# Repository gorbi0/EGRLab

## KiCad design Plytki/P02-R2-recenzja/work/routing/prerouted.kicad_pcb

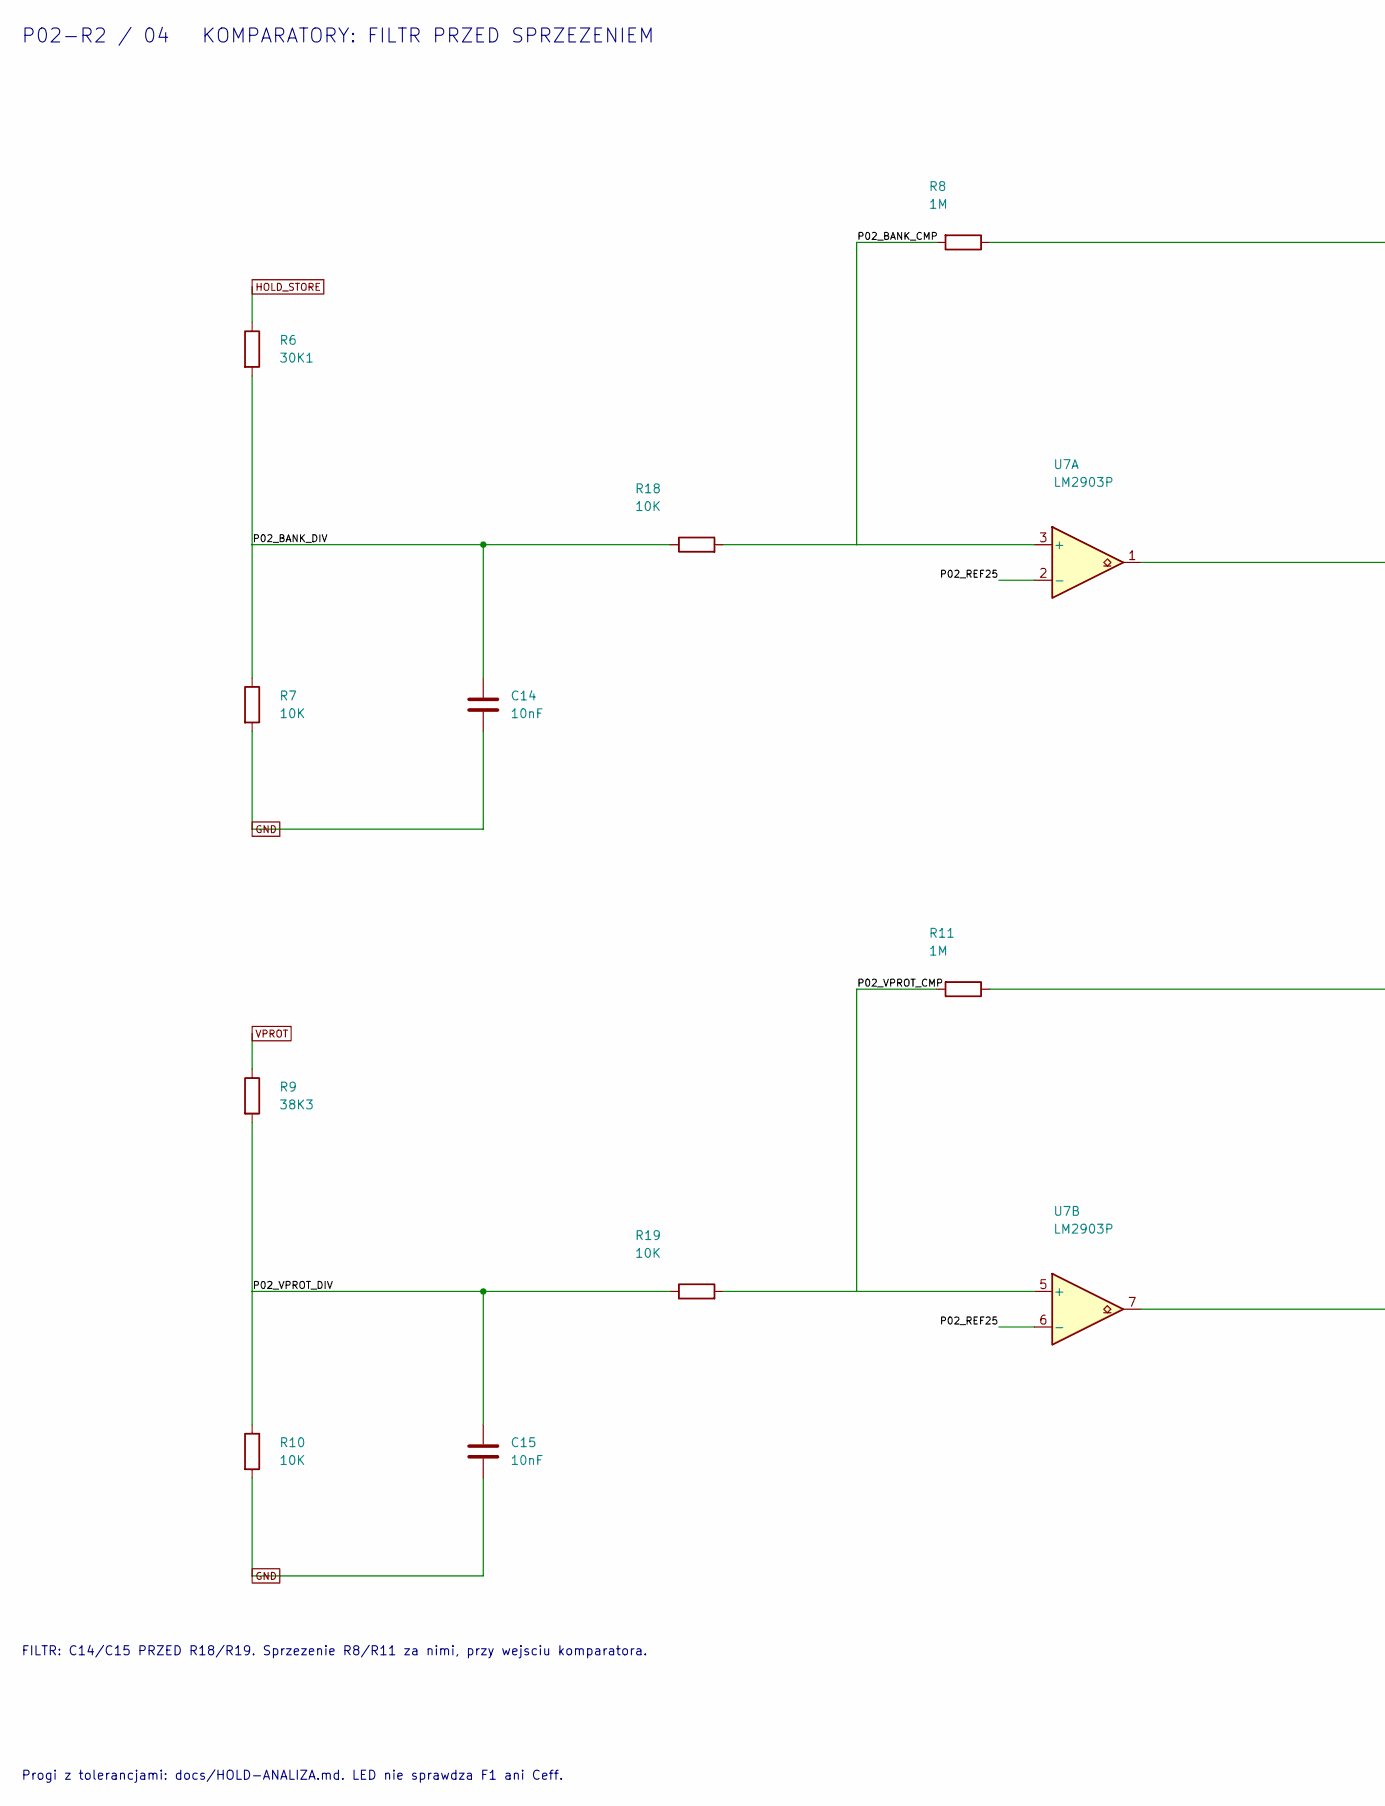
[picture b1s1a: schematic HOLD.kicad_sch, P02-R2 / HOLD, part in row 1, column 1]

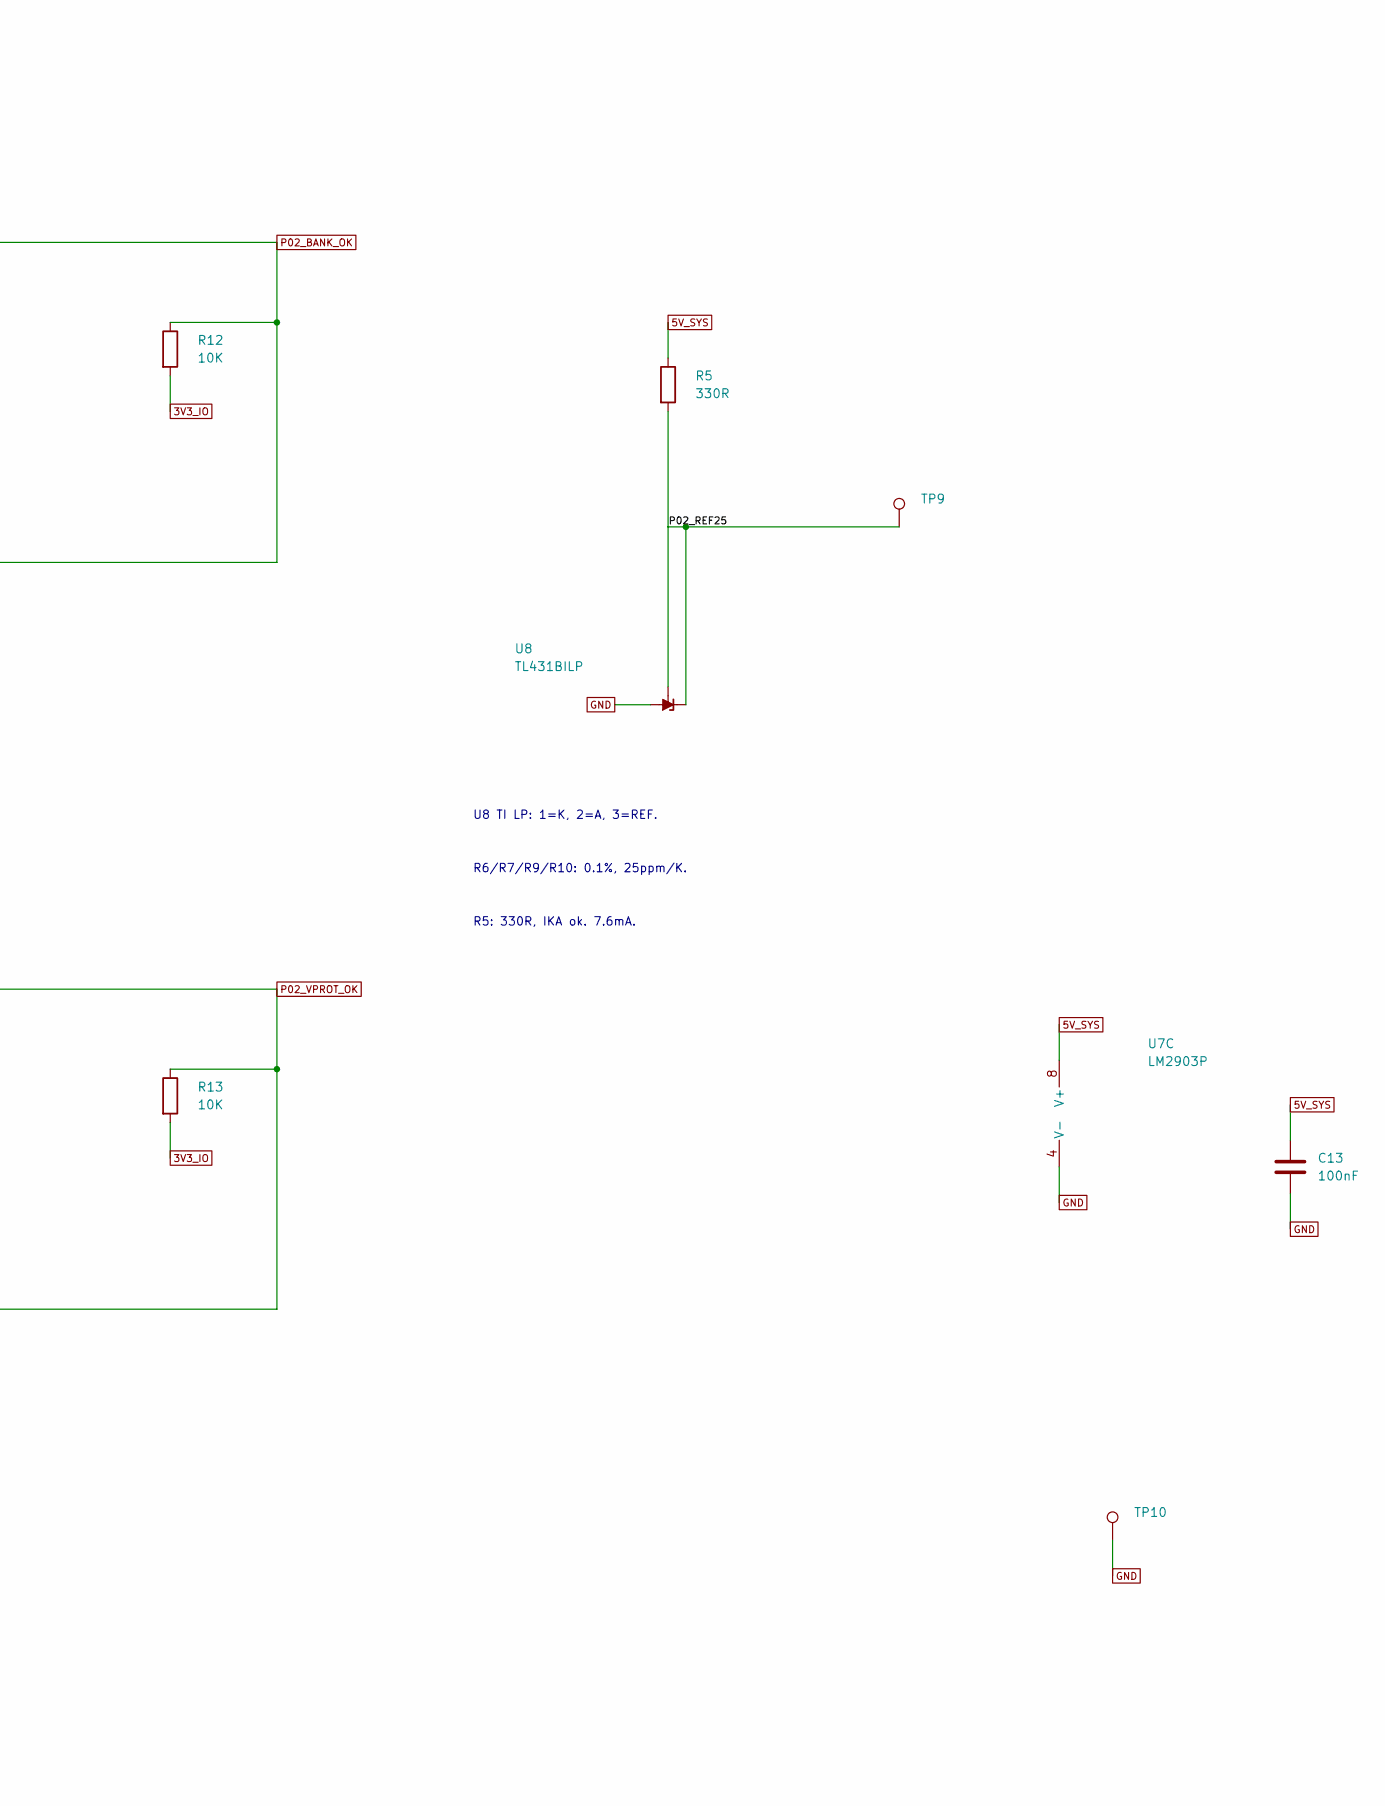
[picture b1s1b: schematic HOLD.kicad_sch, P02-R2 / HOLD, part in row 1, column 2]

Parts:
C13: 100nF; C_Vishay_K15_H5_P5; MPN K104K15X7RF53H5
C14, C15: 10nF; C_Vishay_K15_H5_P5; MPN K103K15X7RF53H5
R5: 330R; R_Axial_DIN0207_L6.3mm_D2.5mm_P10.16mm_Horizontal; MPN MF0207FTE-330R
R6: 30K1; R_Axial_DIN0207_L6.3mm_D2.5mm_P10.16mm_Horizontal; MPN MBB0207VD3012BC100
R7, R10: 10K; R_Axial_DIN0207_L6.3mm_D2.5mm_P10.16mm_Horizontal; MPN MBB0207VD1002BC100
R8, R11: 1M; R_Axial_DIN0207_L6.3mm_D2.5mm_P10.16mm_Horizontal; MPN MF0207FTE-1M
R9: 38K3; R_Axial_DIN0207_L6.3mm_D2.5mm_P10.16mm_Horizontal; MPN MBB0207VD3832BC100
R12, R13, R18, R19: 10K; R_Axial_DIN0207_L6.3mm_D2.5mm_P10.16mm_Horizontal; MPN MF0207FTE-10K
TP9, TP10: TestPad_1; MPN PCB test pad
U7: LM2903P; DIP-8_W7.62mm; MPN LM2903P
U8: TL431BILP; TO-92_Inline_Wide; MPN TL431BILP

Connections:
3V3_IO: R12.2, R13.2; also elsewhere on the board
5V_SYS: C13.1, R5.1, U7.8 (V+); also elsewhere on the board
/HOLD/P02_BANK_CMP: R8.2, R18.2, U7.3 (+)
/HOLD/P02_BANK_DIV: C14.1, R6.2, R7.1, R18.1
/HOLD/P02_REF25: R5.2, TP9.1, U7.2 (-), U7.6 (-), U8.1 (K), U8.3 (REF)
/HOLD/P02_VPROT_CMP: R11.2, R19.2, U7.5 (+)
/HOLD/P02_VPROT_DIV: C15.1, R9.2, R10.1, R19.1
GND: C13.2, C14.2, C15.2, R7.2, R10.2, TP10.1, U7.4 (V-), U8.2 (A); also elsewhere on the board
HOLD_STORE: R6.1; also elsewhere on the board
P02_BANK_OK: R8.1, R12.1, U7.1; also elsewhere on the board
P02_VPROT_OK: R11.1, R13.1, U7.7; also elsewhere on the board
VPROT: R9.1; also elsewhere on the board

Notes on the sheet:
P02-R2 / 04 KOMPARATORY: FILTR PRZED SPRZEZENIEM
FILTR: C14/C15 PRZED R18/R19. Sprzezenie R8/R11 za nimi, przy wejsciu komparatora.
Progi z tolerancjami: docs/HOLD-ANALIZA.md. LED nie sprawdza F1 ani Ceff.
U8 TI LP: 1=K, 2=A, 3=REF.
R6/R7/R9/R10: 0.1%, 25ppm/K.
R5: 330R, IKA ok. 7.6mA.

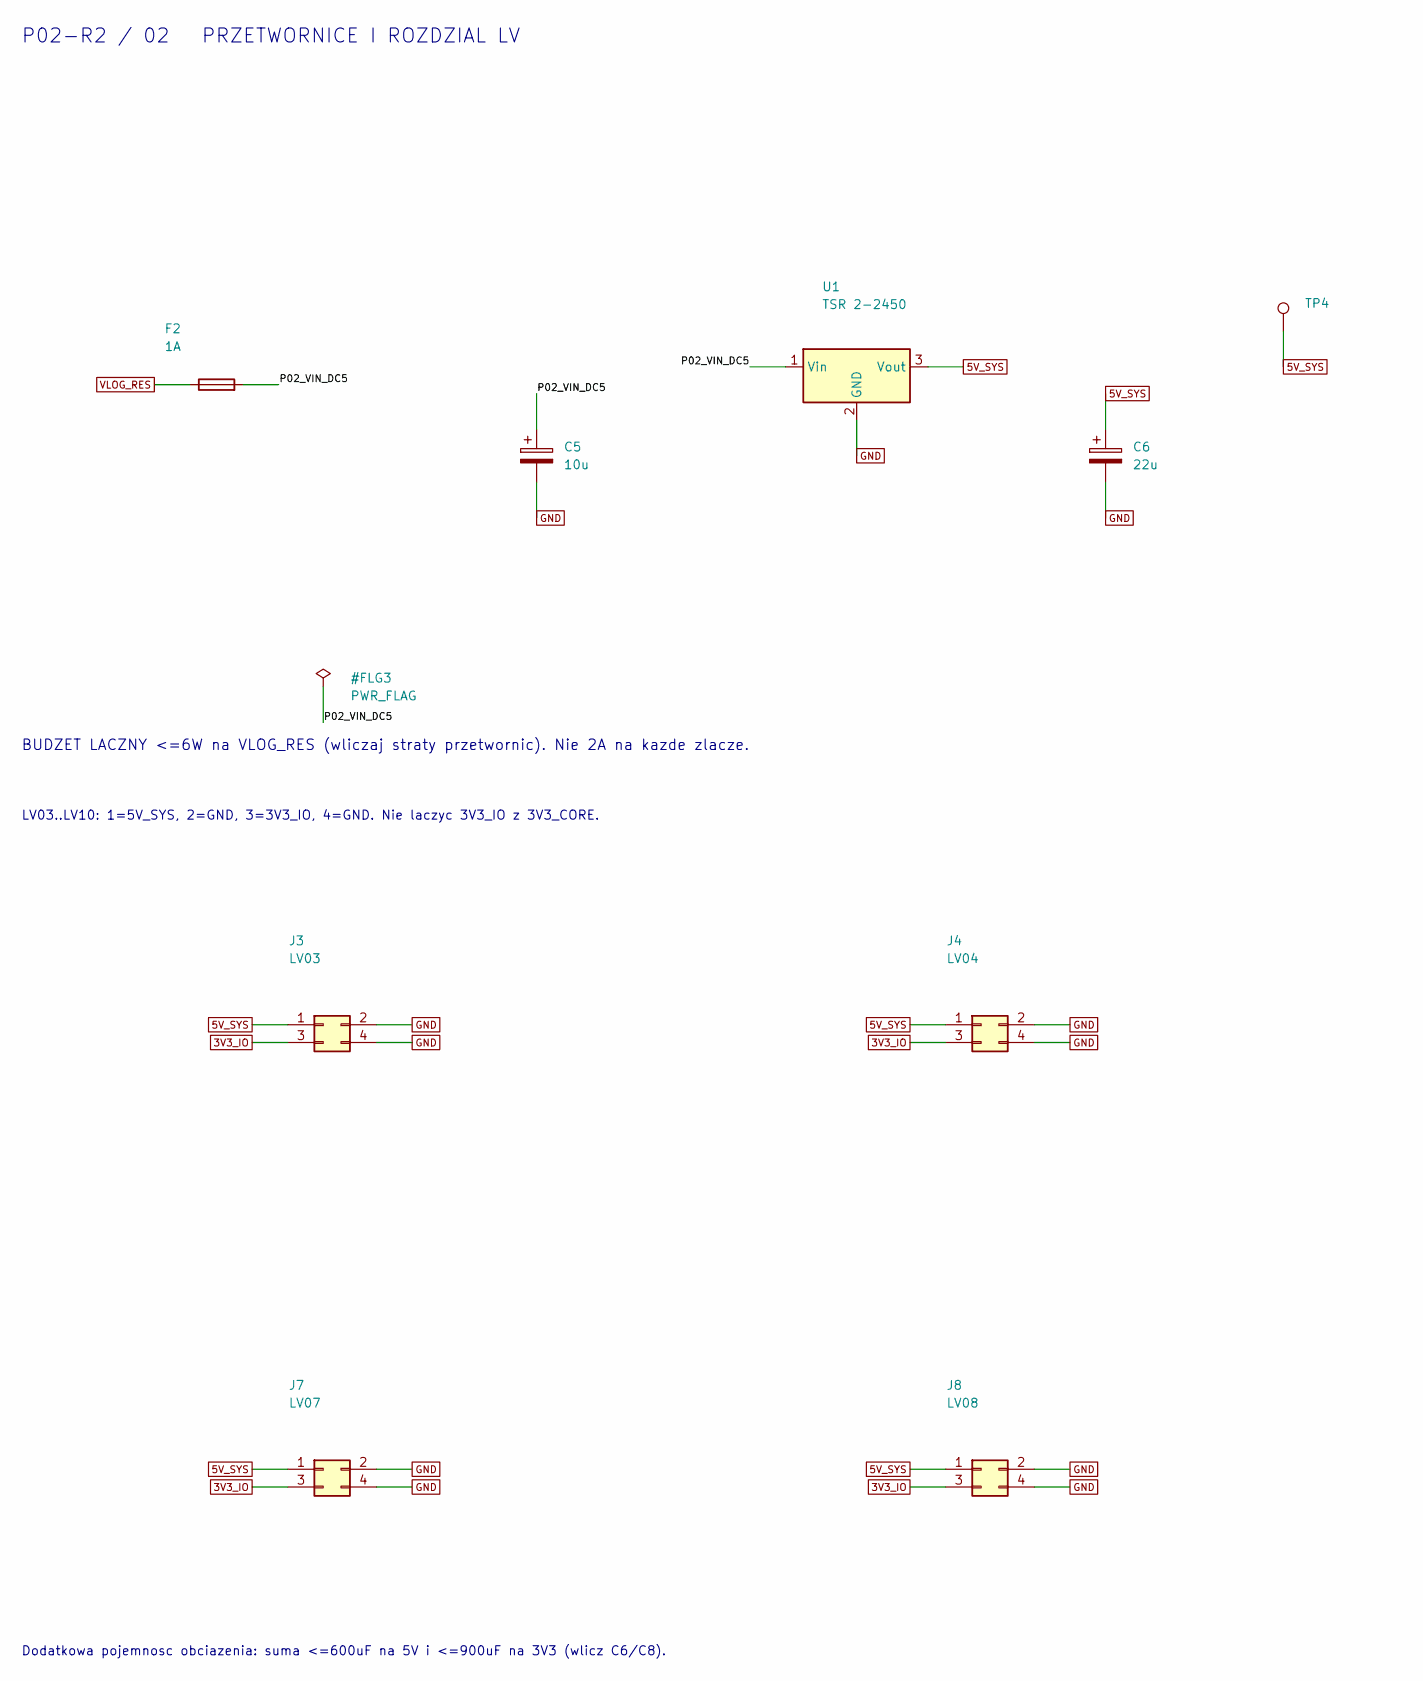
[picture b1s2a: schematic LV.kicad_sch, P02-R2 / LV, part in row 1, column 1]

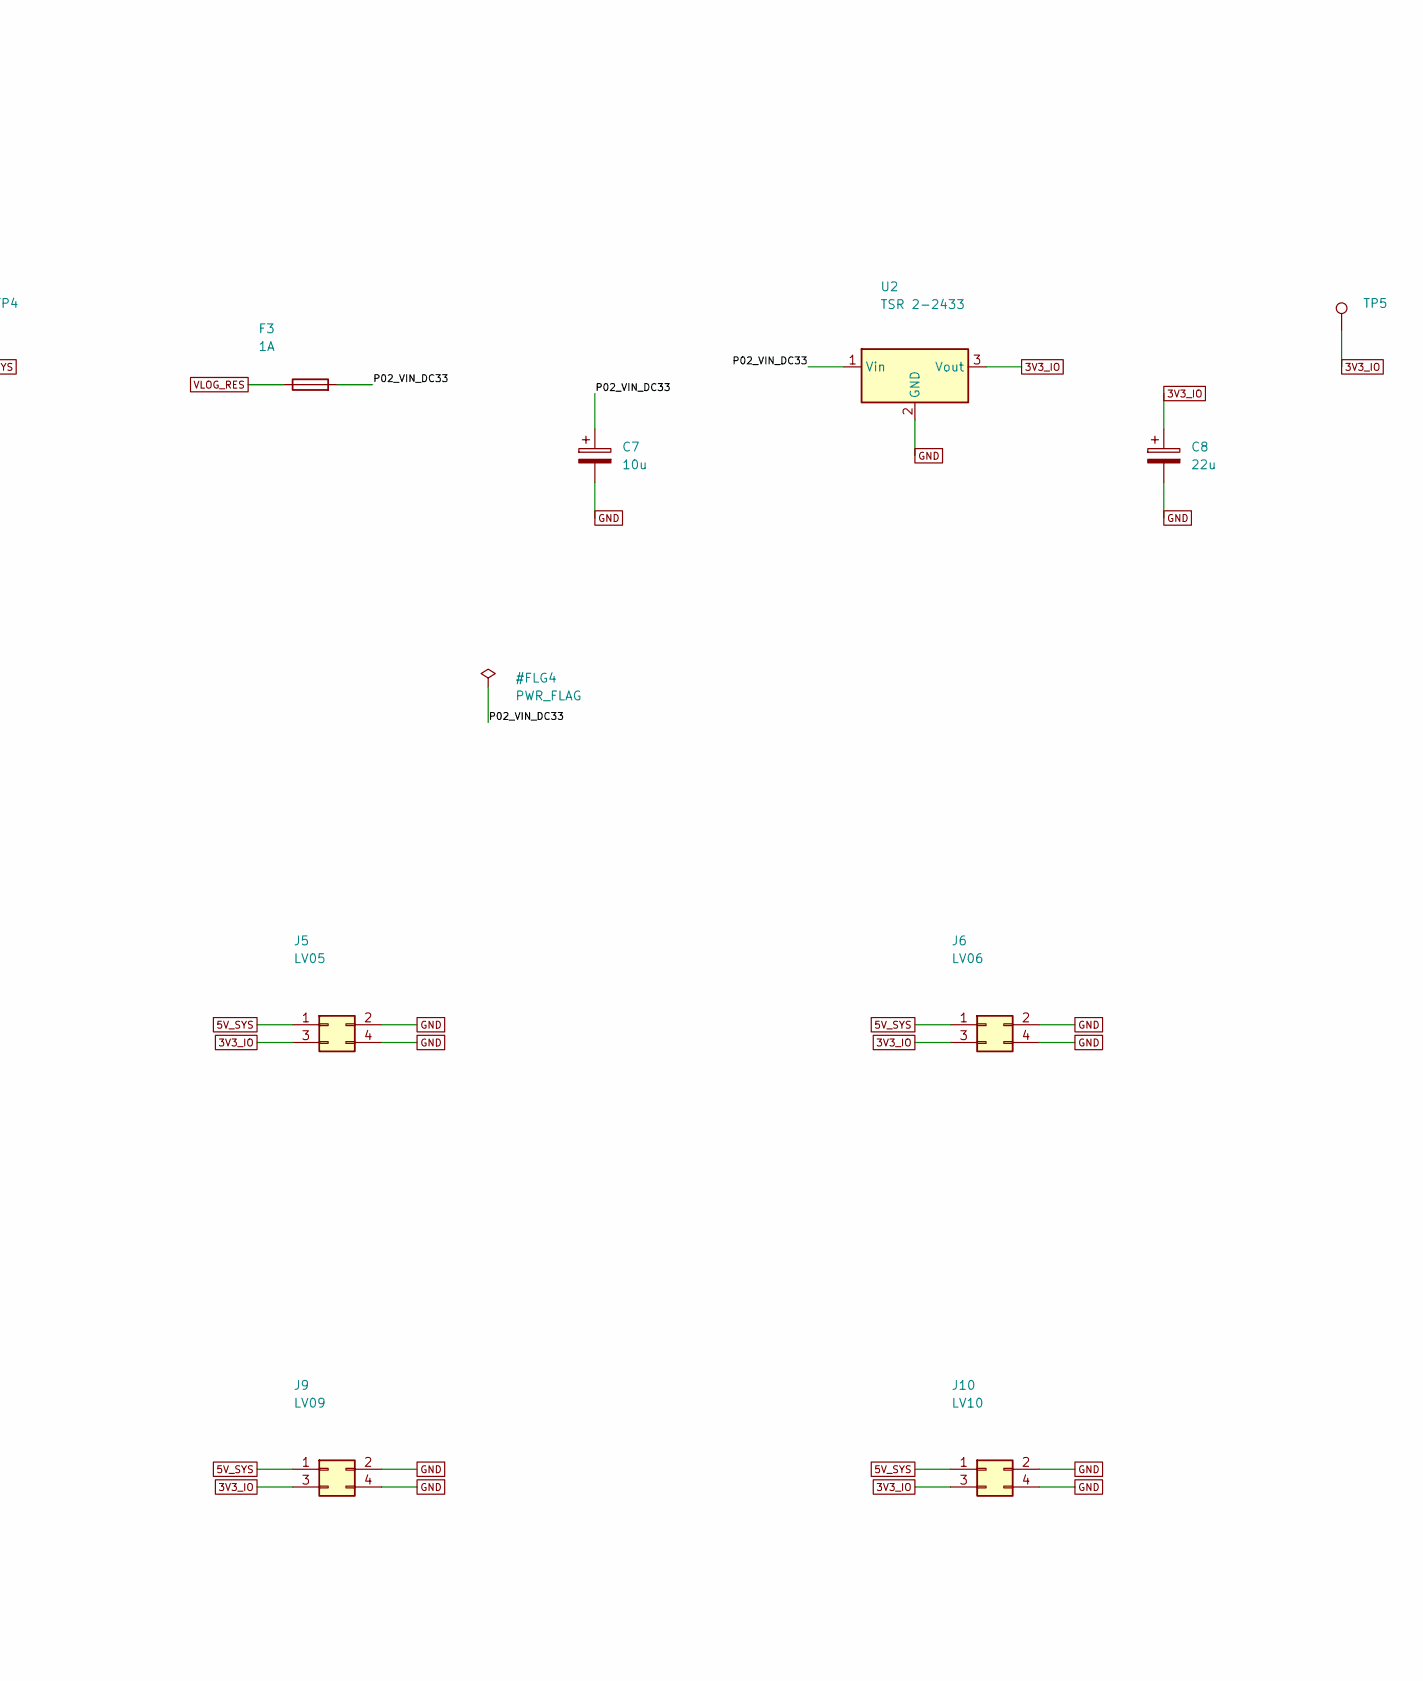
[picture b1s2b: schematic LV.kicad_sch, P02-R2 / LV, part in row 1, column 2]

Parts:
C5, C7: 10u; CP_Radial_D5.0mm_P2.00mm; MPN EEUFR1H100
C6, C8: 22u; CP_Radial_D5.0mm_P2.00mm; MPN EEUFR1C220
F2, F3: 1A; Fuseholder_Cylinder-5x20mm_Stelvio-Kontek_PTF78_Horizontal_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; MPN Stelvio-Kontek PTF78 + fuse F1A DC-rate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
J3: LV03; Molex_Mini-Fit_Jr_5566-04A_2x02_P4.20mm_Vertical; MPN Molex 39-29-6048 (Au, vertical, no snap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
J4: LV04; Molex_Mini-Fit_Jr_5566-04A_2x02_P4.20mm_Vertical; MPN Molex 39-29-6048 (Au, vertical, no snap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
J5: LV05; Molex_Mini-Fit_Jr_5566-04A_2x02_P4.20mm_Vertical; MPN Molex 39-29-6048 (Au, vertical, no snap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
J6: LV06; Molex_Mini-Fit_Jr_5566-04A_2x02_P4.20mm_Vertical; MPN Molex 39-29-6048 (Au, vertical, no snap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
J7: LV07; Molex_Mini-Fit_Jr_5566-04A_2x02_P4.20mm_Vertical; MPN Molex 39-29-6048 (Au, vertical, no snap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
J8: LV08; Molex_Mini-Fit_Jr_5566-04A_2x02_P4.20mm_Vertical; MPN Molex 39-29-6048 (Au, vertical, no snap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
J9: LV09; Molex_Mini-Fit_Jr_5566-04A_2x02_P4.20mm_Vertical; MPN Molex 39-29-6048 (Au, vertical, no snap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
J10: LV10; Molex_Mini-Fit_Jr_5566-04A_2x02_P4.20mm_Vertical; MPN Molex 39-29-6048 (Au, vertical, no snap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
TP4, TP5: TestPad_1; MPN PCB test pad
U1: TSR 2-2450; Converter_DCDC_TRACO_TSR2-xxxx_THT; MPN TSR 2-2450
U2: TSR 2-2433; Converter_DCDC_TRACO_TSR2-xxxx_THT; MPN TSR 2-2433

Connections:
3V3_IO: C8.1, J3.3, J4.3, J5.3, J6.3, J7.3, J8.3, J9.3, J10.3, TP5.1, U2.3 (Vout); also elsewhere on the board
5V_SYS: C6.1, J3.1, J4.1, J5.1, J6.1, J7.1, J8.1, J9.1, J10.1, TP4.1, U1.3 (Vout); also elsewhere on the board
/LV/P02_VIN_DC5: C5.1, F2.2, U1.1 (Vin)
/LV/P02_VIN_DC33: C7.1, F3.2, U2.1 (Vin)
GND: C5.2, C6.2, C7.2, C8.2, J3.2, J3.4, J4.2, J4.4, J5.2, J5.4, J6.2, J6.4, J7.2, J7.4, J8.2, J8.4, J9.2, J9.4, J10.2, J10.4, U1.2 (GND), U2.2 (GND); also elsewhere on the board
VLOG_RES: F2.1, F3.1; also elsewhere on the board

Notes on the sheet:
P02-R2 / 02 PRZETWORNICE I ROZDZIAL LV
BUDZET LACZNY <=6W na VLOG_RES (wliczaj straty przetwornic). Nie 2A na kazde zlacze.
LV03..LV10: 1=5V_SYS, 2=GND, 3=3V3_IO, 4=GND. Nie laczyc 3V3_IO z 3V3_CORE.
Dodatkowa pojemnosc obciazenia: suma <=600uF na 5V i <=900uF na 3V3 (wlicz C6/C8).

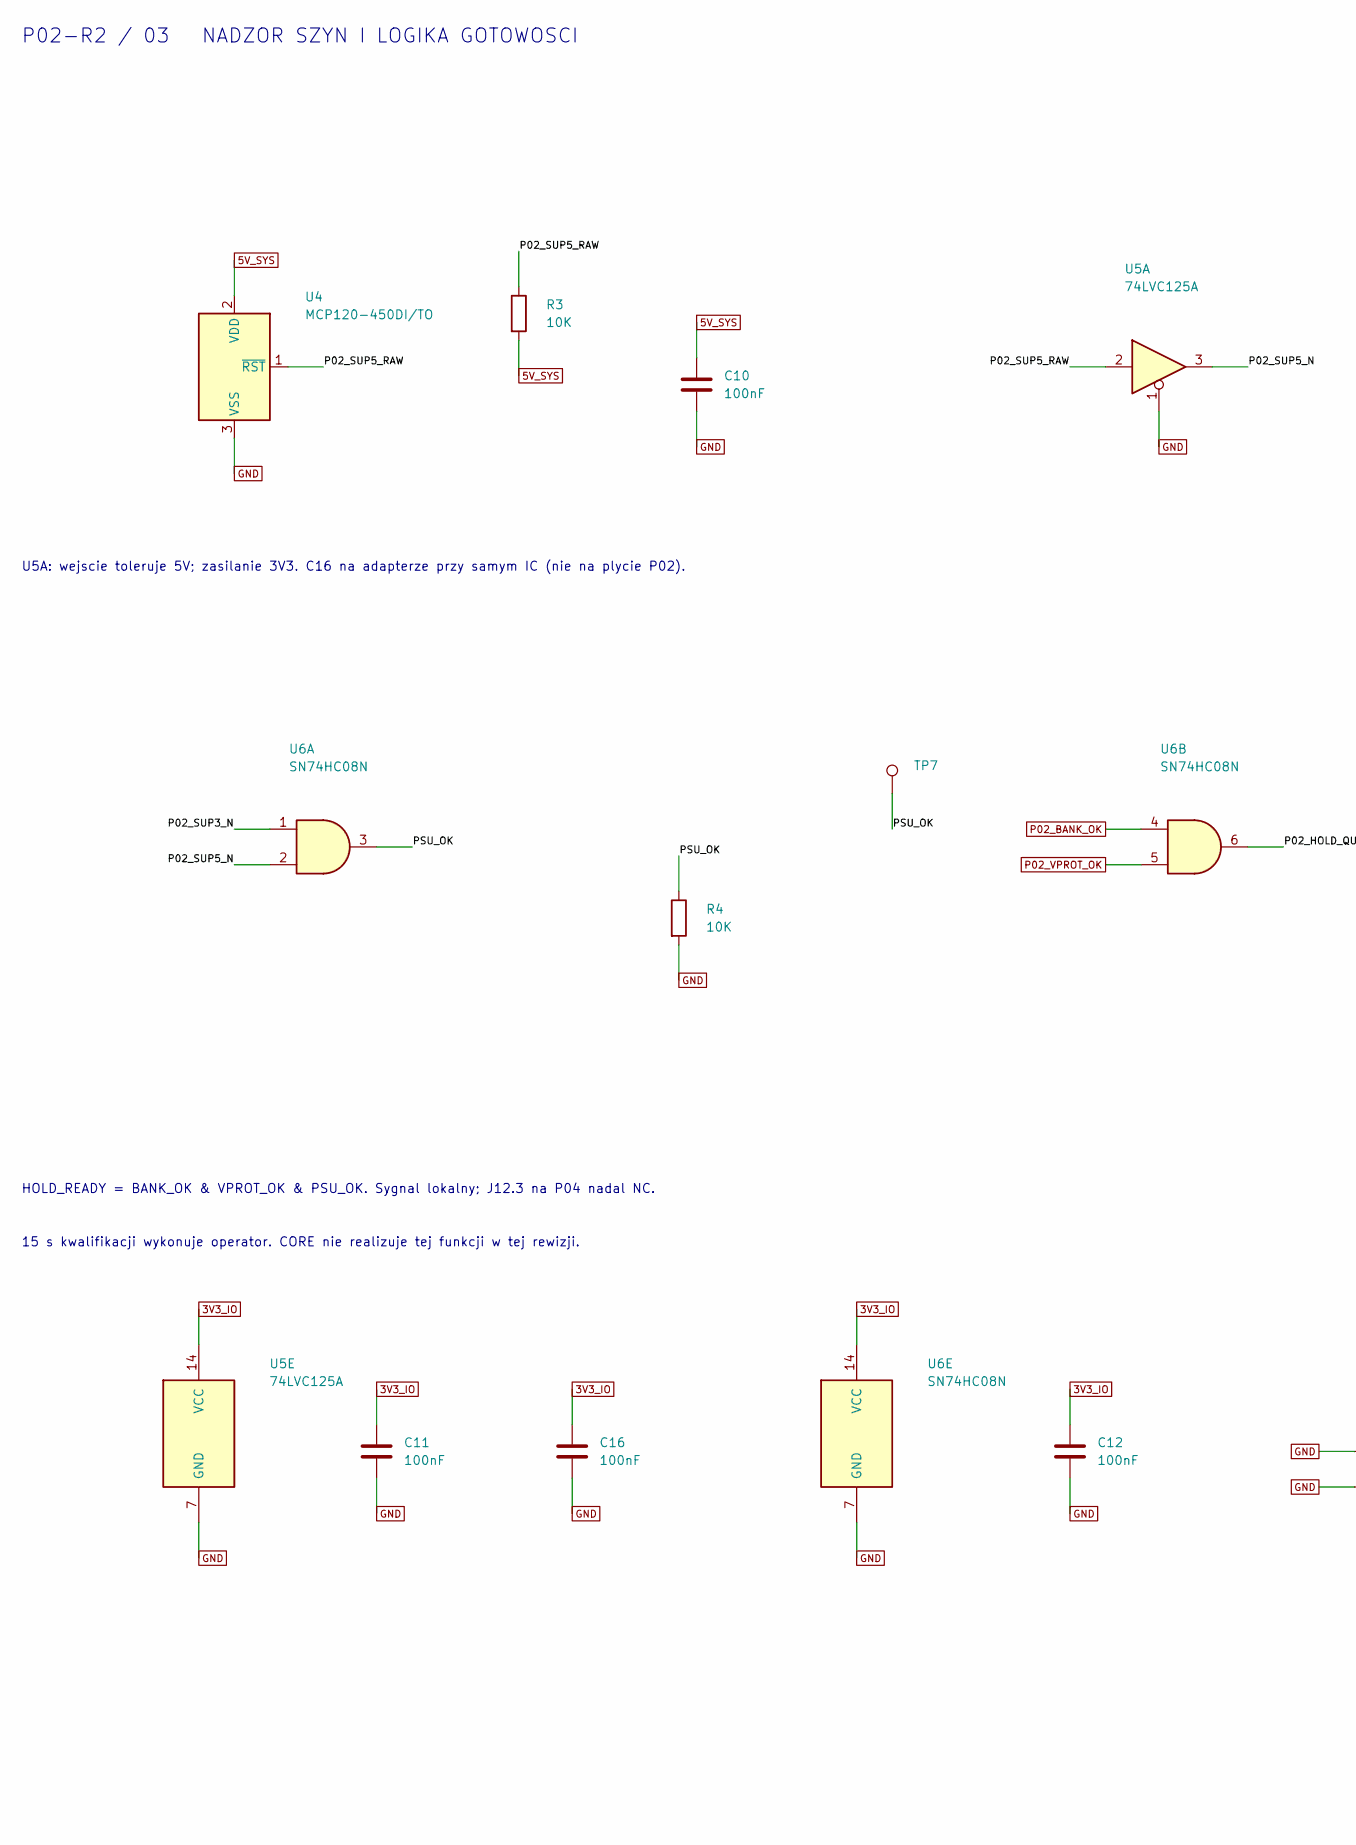
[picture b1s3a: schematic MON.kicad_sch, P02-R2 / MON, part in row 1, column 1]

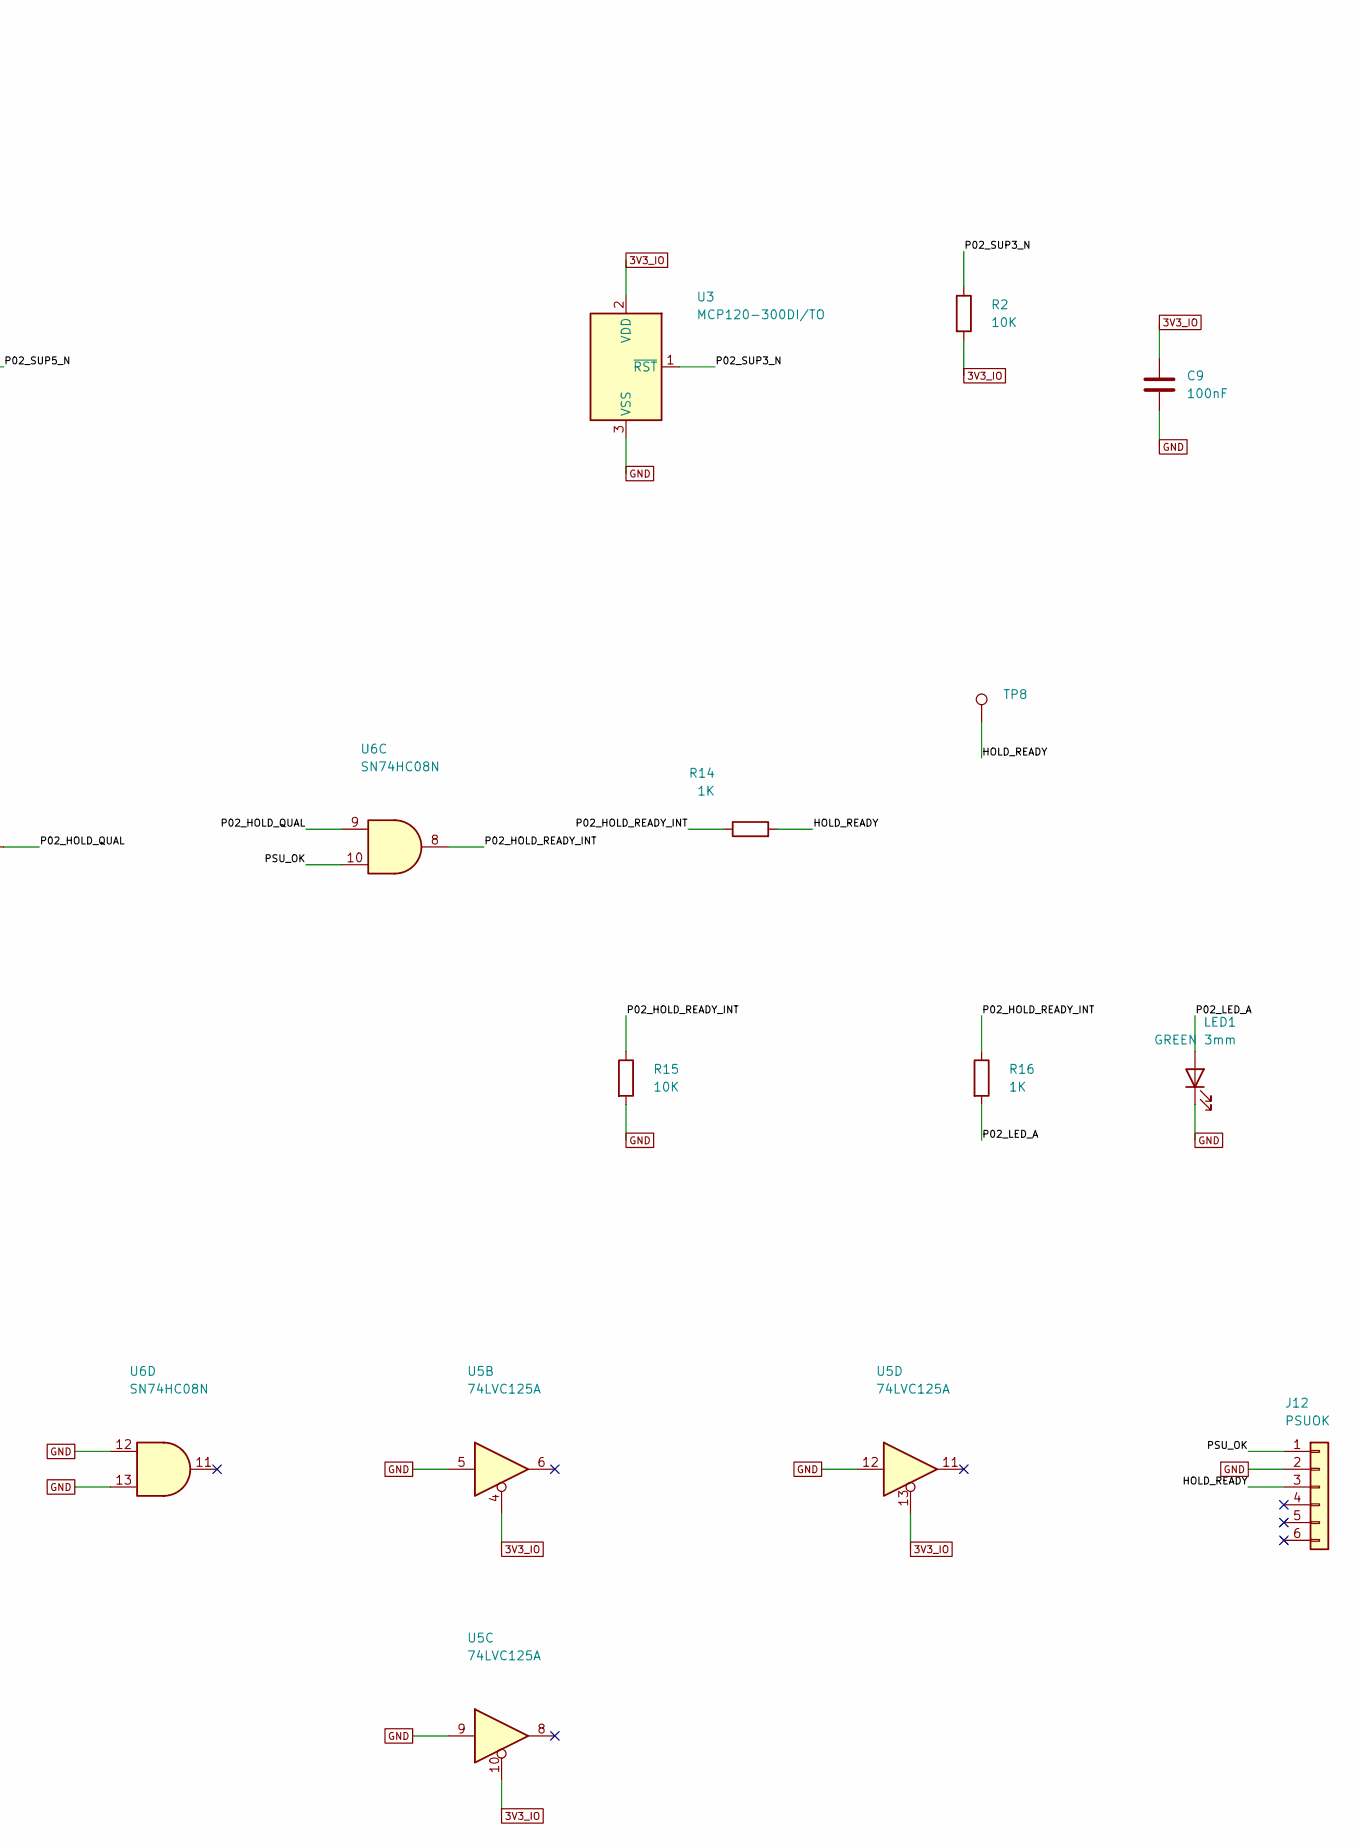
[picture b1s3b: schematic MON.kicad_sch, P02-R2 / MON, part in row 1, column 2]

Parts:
C9, C10, C11, C12: 100nF; C_Vishay_K15_H5_P5; MPN K104K15X7RF53H5
C16: 100nF; MPN GRM21BR71H104KA01L (0805)
J12: PSUOK; Pigtail_PSUOK_6x_P2.54; MPN PCB termination; H_PSUOK
LED1: GREEN 3mm; LED_D3.0mm; MPN L-934GD
R2, R3, R4, R15: 10K; R_Axial_DIN0207_L6.3mm_D2.5mm_P10.16mm_Horizontal; MPN MF0207FTE-10K
R14, R16: 1K; R_Axial_DIN0207_L6.3mm_D2.5mm_P10.16mm_Horizontal; MPN MF0207FTE-1K
TP7, TP8: TestPad_1; MPN PCB test pad
U3: MCP120-300DI/TO; TO-92_Inline_Wide; MPN MCP120-300DI/TO
U4: MCP120-450DI/TO; TO-92_Inline_Wide; MPN MCP120-450DI/TO
U5: 74LVC125A; Adapter_SO14_DIP14_W15.24_Kamami575068; MPN 74LVC125AD,118 (Nexperia) on Kamami 575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
U6: SN74HC08N; DIP-14_W7.62mm; MPN SN74HC08N

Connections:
3V3_IO: C9.1, C11.1, C12.1, C16.1, R2.2, U3.2 (VDD), U5.4, U5.10, U5.13, U5.14 (VCC), U6.14 (VCC); also elsewhere on the board
5V_SYS: C10.1, R3.2, U4.2 (VDD); also elsewhere on the board
/MON/HOLD_READY: J12.3, R14.2, TP8.1
/MON/P02_HOLD_QUAL: U6.6, U6.9
/MON/P02_HOLD_READY_INT: R14.1, R15.1, R16.1, U6.8
/MON/P02_LED_A: LED1.2 (A), R16.2
/MON/P02_SUP3_N: R2.1, U3.1 (~RST), U6.1
/MON/P02_SUP5_N: U5.3, U6.2
/MON/P02_SUP5_RAW: R3.1, U4.1 (~RST), U5.2
/MON/PSU_OK: J12.1, R4.1, TP7.1, U6.3, U6.10
GND: C9.2, C10.2, C11.2, C12.2, C16.2, J12.2, LED1.1 (K), R4.2, R15.2, U3.3 (VSS), U4.3 (VSS), U5.1, U5.5, U5.7 (GND), U5.9, U5.12, U6.7 (GND), U6.12, U6.13; also elsewhere on the board
P02_BANK_OK: U6.4; also elsewhere on the board
P02_VPROT_OK: U6.5; also elsewhere on the board

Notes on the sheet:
P02-R2 / 03 NADZOR SZYN I LOGIKA GOTOWOSCI
U5A: wejscie toleruje 5V; zasilanie 3V3. C16 na adapterze przy samym IC (nie na plycie P02).
HOLD_READY = BANK_OK & VPROT_OK & PSU_OK. Sygnal lokalny; J12.3 na P04 nadal NC.
15 s kwalifikacji wykonuje operator. CORE nie realizuje tej funkcji w tej rewizji.
